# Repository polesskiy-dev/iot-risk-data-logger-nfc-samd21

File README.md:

# IoT Risk Data Logger

## Introduction
Fully open-source and open-hardware **data logger** tailored for logistics applications i.e. for cold chain monitoring systems.

## Hardware

[Schematics, PCB, enclosure, BOM, assembly documentation](https://github.com/polesskiy-dev/iot-risk-data-logger-nfc-samd21-hardware)

### Features

#### Key risk metrics:
- Temperature/Humidity [Sensirion SHT3x](https://sensirion.com/media/documents/213E6A3B/63A5A569/Datasheet_SHT3x_DIS.pdf)
- Ambient Light Sensor [TI OPT3001](https://www.ti.com/lit/ds/symlink/opt3001.pdf?ts=1694786594042&ref_url=https%253A%252F%252Fwww.ti.com%252Fproduct%252FOPT3001)
- Shock Sensor - Accelerometer [NXP MMA8452Q](https://www.nxp.com/docs/en/data-sheet/MMA8452Q.pdf)

#### Communication:
- USB-C:
    - MSD: Device works ad a flash drive to direct log read on PC
    - CDC: Console for debug and firmware bootloader
- NFC for control through mobile app [ST ST25DV04K](https://www.st.com/resource/en/datasheet/st25dv04k.pdf)

#### Security:
- Hardware crypto [Microchip ATECC608A](https://www.microchip.com/wwwproducts/en/ATECC608A) for:
    - Firmware encryption for bootloader
    - Log data encryption
    - Authentication (X509 certificates for IoT platforms)

#### Power:
- Powered by 2xAAA batteries or USB-C (reverse polarity protection, OR source selection)
- Low Power Consumption: Ultra-low power architecture, ~ one year of data acquisition

#### Additional Features:
- 4MB SPI NOR Flash [AT25DF321](https://www.mouser.com/catalog/specsheets/atmel_doc3669.pdf?_gl=1*5ifz1l*_ga*NTg5MTc1OTE2LjE2ODkwMTAyMDY.*_ga_15W4STQT4T*MTY5NDg2NDM4MS4yMS4wLjE2OTQ4NjQzODIuMC4wLjA.*_ga_1KQLCYKRX3*MTY5NDg2NDM4MS4yMS4wLjE2OTQ4NjQzODIuNTkuMC4w)
- RTC Clock: accurate 32.768Hz quartz oscillator
- LED: Simple indication for device states

#### Main MCU
- [Microchip ATSAMD21E18](https://www.microchip.com/en-us/product/atsamd21e18) - 32-bit ARM Cortex-M0+ MCU, 48MHz, 256KB of flash and 32KB of SRAM. Satisfies AEC-Q100, recommended for Automotive.

## Firmware

The firmware is written in C with a bare-metal approach and exclusively uses static memory allocation. It is developed on top of the [Harmony v3](https://www.microchip.com/en-us/tools-resources/configure/mplab-harmony) Embedded Software framework. Developed with [MPLAB X](https://www.microchip.com/en-us/tools-resources/develop/mplab-x-ide), [XC32](https://www.microchip.com/en-us/tools-resources/develop/mplab-xc-compilers) compiler.

### Main architecture

The source code adheres to an asynchronous, non-blocking programming style designed to achieve ultra-low power consumption.

The core mechanism revolves around handling asynchronous events from a queue and entering a low-power sleep state when the queue is empty. New events are enqueued either through interrupts (e.g., cron-scheduled sensor reads) or through the main system loop.

The architecture incorporates the following key concepts:
- [Event Loop](https://en.wikipedia.org/wiki/Event_loop)
- [Actor Model](https://en.wikipedia.org/wiki/Actor_model) - aka [Active Object](https://en.wikipedia.org/wiki/Active_object)
- [Finite-state machine](https://en.wikipedia.org/wiki/Finite-state_machine) - [Mealy](https://en.wikipedia.org/wiki/Mealy_machine) + [Moore](https://en.wikipedia.org/wiki/Moore_machine) implementation

To streamline development, an Active Object + FSM library has been implemented and is maintained in a separate [active-object-fsm](https://github.com/polesskiy-dev/active-object-fsm) repository.

## Installation
    
    $ git clone https://github.com/polesskiy-dev/iot-risk-data-logger-nfc-samd21 --recurse-submodules

Update submodules to the latest version (optional):

    $ git submodule init && git submodule update --remote # install submodules

## Some dev process photos:

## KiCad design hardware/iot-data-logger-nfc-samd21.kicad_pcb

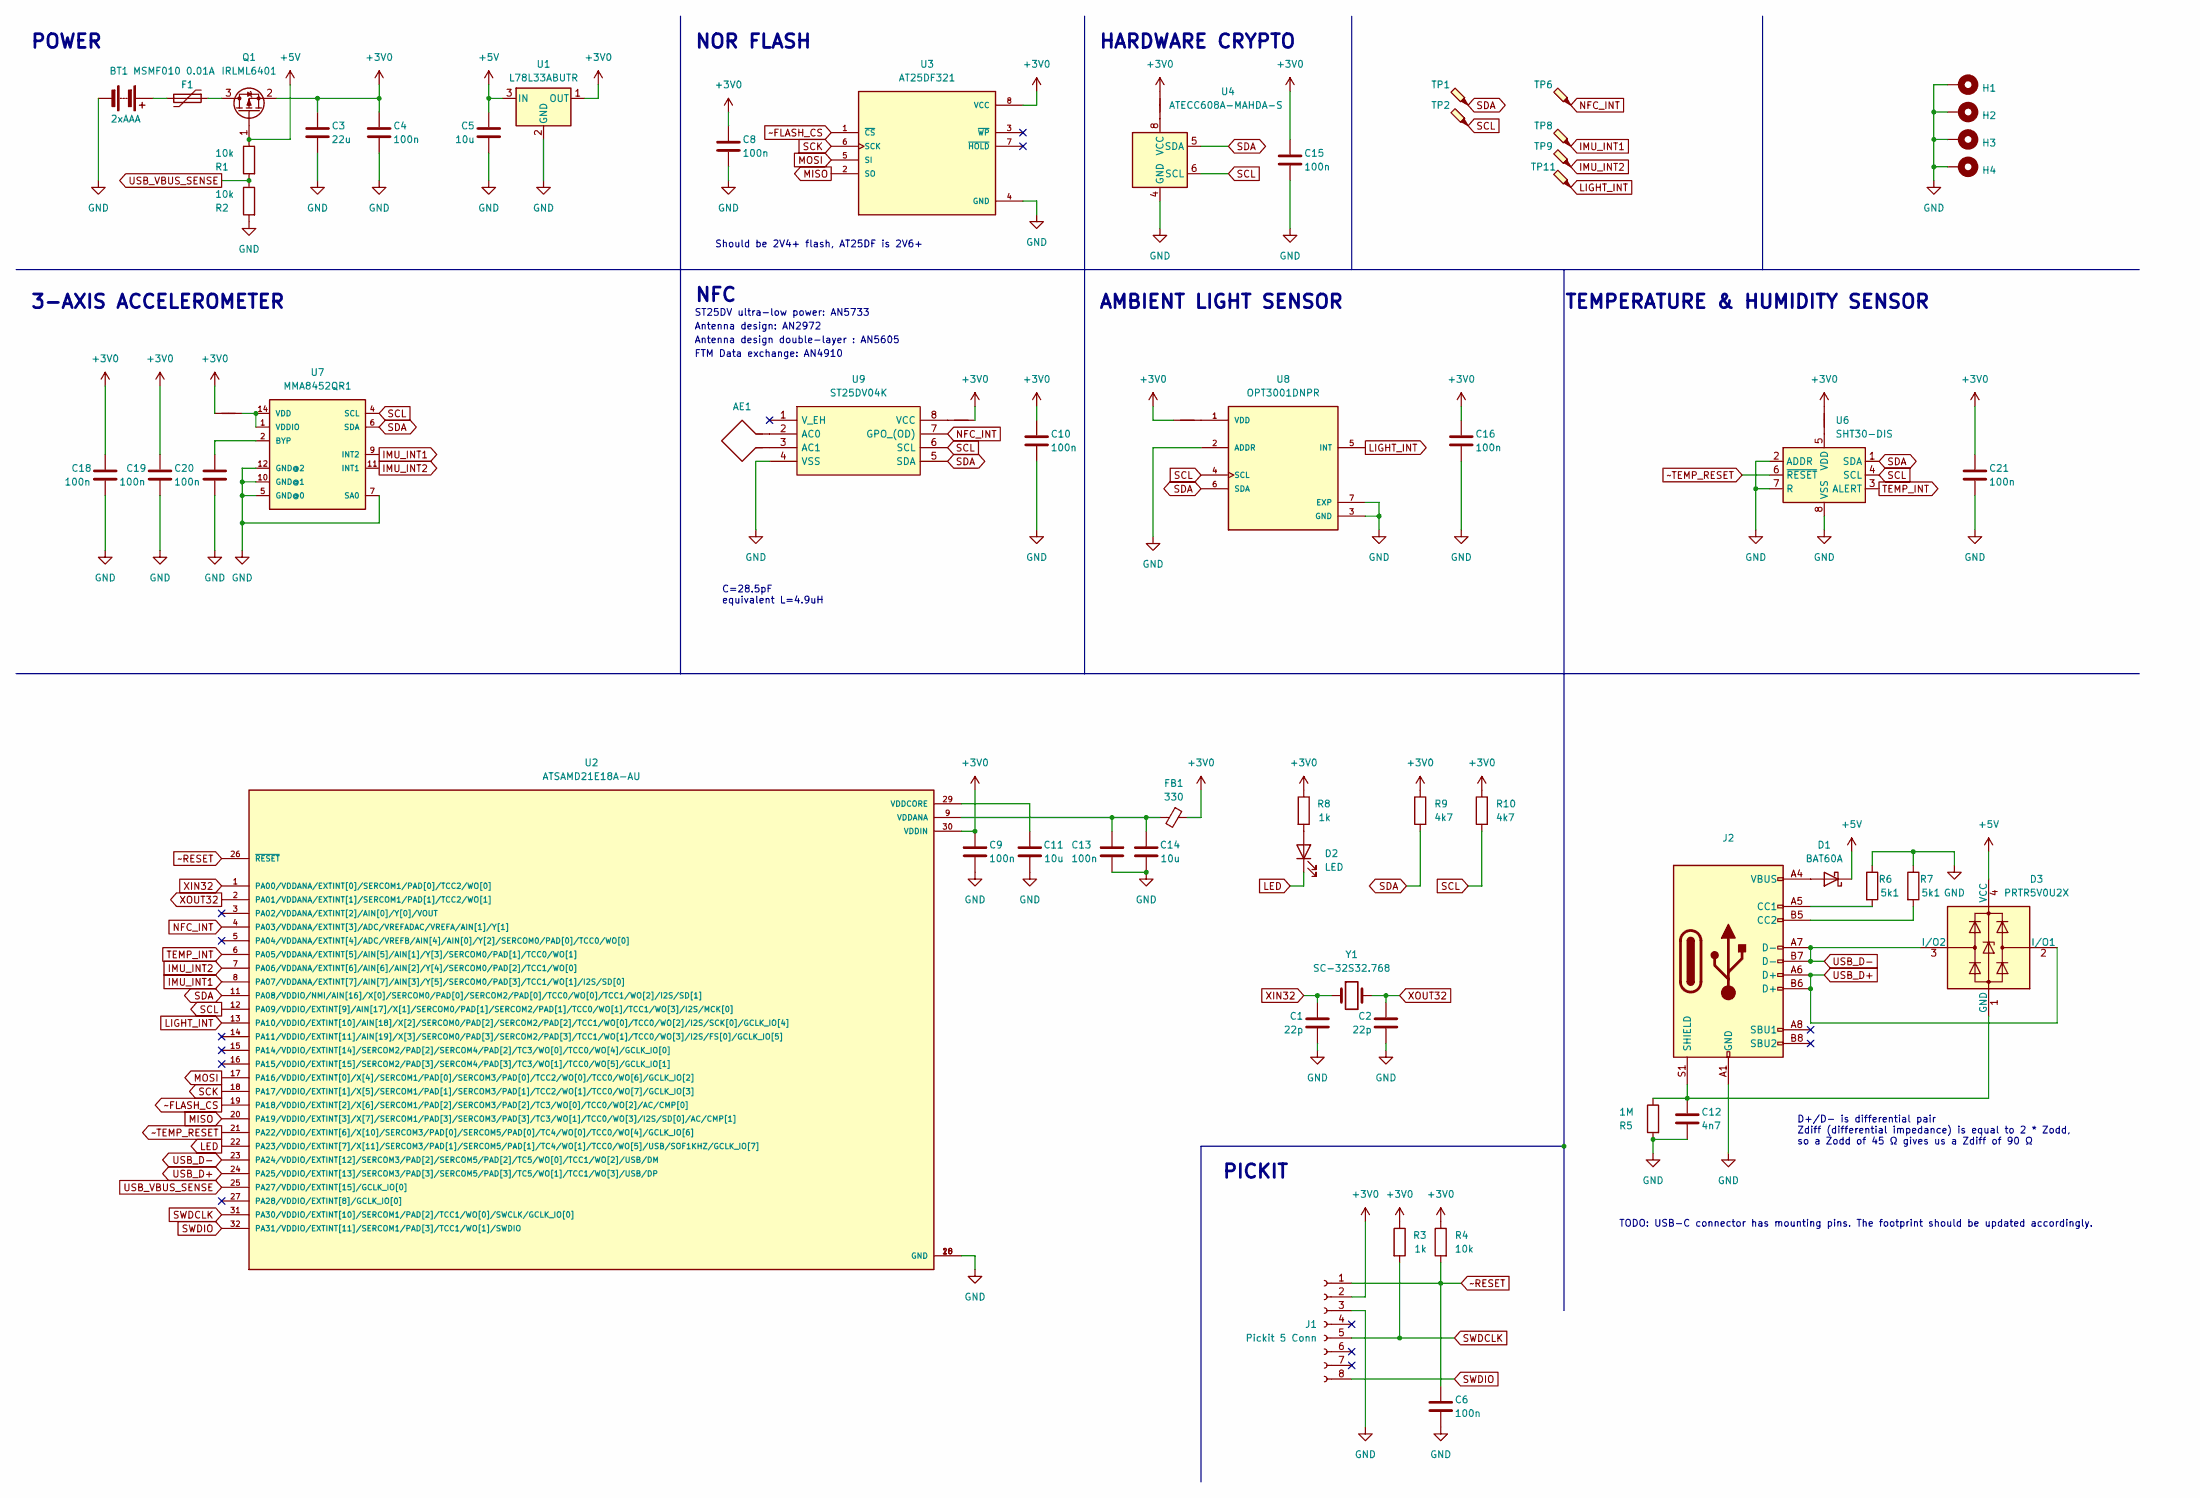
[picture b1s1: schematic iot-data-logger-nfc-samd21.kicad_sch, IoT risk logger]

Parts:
AE1: Antenna_Loop; ANT_NFC_30x40
BT1: 2xAAA; BatteryHolder_Keystone_2468_2xAAA; Part Keystone 2468; LCSC Part C254917
C1, C2: 22p; C_0805_2012Metric_Pad1.18x1.45mm_HandSolder; Part CL21C220JBANNNC; LCSC Part C1804
C3: 22u; C_1206_3216Metric_Pad1.33x1.80mm_HandSolder; Part CL31A226KAHNNNE; LCSC Part C12891
C4, C6, C8, C9, C10, C13, C15, C16, C18, C19, C20, C21: 100n; C_0805_2012Metric_Pad1.18x1.45mm_HandSolder; Part CL21B104KBCNNNC; LCSC Part C1711
C5, C11, C14: 10u; C_0805_2012Metric_Pad1.18x1.45mm_HandSolder; Part CL21A106KOQNNNE; LCSC Part C1713
C12: 4n7; C_0805_2012Metric_Pad1.18x1.45mm_HandSolder; Part CL21B472KBANNNC; LCSC Part C50131
D1: BAT60A; D_SOD-323_HandSoldering; Part BAT60A; LCSC Part C5355496
D2: LED; LED_0805_2012Metric_Pad1.15x1.40mm_HandSolder; Part NCD0805G1; LCSC Part C84260
D3: PRTR5V0U2X; SOT-143; Part PRTR5V0U2X; LCSC Part C2827688
F1: MSMF010 0.01A; Fuse_1812_4532Metric_Pad1.30x3.40mm_HandSolder; Part MF-MSMF010-2; LCSC Part C12430
FB1: 330; R_0805_2012Metric_Pad1.20x1.40mm_HandSolder; Part BLM21PG331SN1D; LCSC Part C47130
H1, H2, H3, H4: MountingHole_Pad; MountingHole_3.2mm_M3_Pad_Via
J1: Pickit 5 Conn; PinSocket_1x08_P2.54mm_Vertical
J2: USB Type-C; USB_C_Receptacle_XKB_U262-16XN-4BVC11; Part KH-TYPE-C-16P; LCSC Part C709357
NT1, NT2, NT3, NT4, NT5: NetTie_2; NetTie-2_SMD_Pad0.5mm
Q1: IRLML6401; SOT-23; Part IRLML6401TRPBF; LCSC Part C3034
R1, R2, R4: 10k; R_0805_2012Metric_Pad1.20x1.40mm_HandSolder; Part RC0805FR-0710KL; LCSC Part C84376
R3, R8: 1k; R_0805_2012Metric_Pad1.20x1.40mm_HandSolder; Part RC0805FR-071KL; LCSC Part C95781
R5: 1M; R_0805_2012Metric_Pad1.20x1.40mm_HandSolder; Part RC0805FR-071ML; LCSC Part C107700
R6, R7: 5k1; R_0805_2012Metric_Pad1.20x1.40mm_HandSolder; Part RC0805FR-075K1L; LCSC Part C84375
R9, R10: 4k7; R_0805_2012Metric_Pad1.20x1.40mm_HandSolder; Part RC0805FR-074K7L; LCSC Part C60816
TP1, TP2, TP6, TP8, TP9, TP11: TestPoint_Probe; TestPoint_THTPad_D1.5mm_Drill0.7mm
U1: L78L33ABUTR; SOT-89-3_Handsoldering; Part L78L33ABUTR; LCSC Part C81362
U2: ATSAMD21E18A-AU; TQFP-32_7x7mm_P0.8mm; Part ATSAMD21E18A-AU; LCSC Part C618771
U3: AT25DF321; SOP-8_5.28x5.23mm_P1.27mm; Part AT25DF321A-SH-T; LCSC Part C6490
U4: ATECC608A-MAHDA-S; DFN-8-1EP_3x2mm_P0.5mm_EP1.3x1.5mm; Part ATECC608A-MAHDA-S; LCSC Part C616908
U6: SHT30-DIS; Sensirion_DFN-8-1EP_2.5x2.5mm_P0.5mm_EP1.1x1.7mm; Part SHT30-DIS-B10KS; LCSC Part C2687423
U7: MMA8452QR1; XDCR_MMA8452QR1; Part MMA8452QR1; LCSC Part C11360
U8: OPT3001DNPR; SON65P200X200X65-7N; Part OPT3001DNPR; LCSC Part C90462
U9: ST25DV04K; TSSOP-8_4.4x3mm_P0.65mm; Part ST25DV04K-IER6T3; LCSC Part C2654816
Y1: SC-32S32.768; Crystal_SMD_EuroQuartz_EQ161-2Pin_3.2x1.5mm_HandSoldering; Part SC-32S32.768kHz20PPM12.5pF; LCSC Part C97606

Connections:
+3V0: C3.1, C4.1, C8.1, C9.1, C10.1, C15.1, C16.1, C18.1, C19.1, C21.1, FB1.1, J1.2, NT1.1, NT2.1, NT3.2, NT4.1, NT5.2, Q1.2 (S), R3.1, R4.1, R8.1, R9.1, R10.1, U1.1 (OUT), U2.30 (VDDIN), U3.8 (VCC)
+5V: C5.1, D1.1 (K), D3.4 (VCC), Q1.1 (G), R1.1, U1.3 (IN)
GND: BT1.2 (-), C1.2, C2.2, C3.2, C4.2, C5.2, C6.2, C8.2, C9.2, C10.2, C11.2, C12.2, C13.2, C14.2, C15.2, C16.2, C18.2, C19.2, C20.2, C21.2, H1.1, H2.1, H3.1, H4.1, J1.3, J2.A1 (GND), J2.A12 (GND), J2.B1 (GND), J2.B12 (GND), R2.2, R5.2, R6.1, R7.1, U1.2 (GND), U2.10 (GND), U2.28 (GND), U3.4 (GND), U4.4 (GND), U6.2 (ADDR), U6.7 (R), U6.8 (VSS), U6.9 (VSS), U7.5 (GND@0), U7.7 (SA0), U7.10 (GND@1), U7.12 (GND@2), U8.2 (ADDR), U8.3 (GND), U8.7 (EXP), U9.4 (VSS)
IMU_INT1: TP8.1, U2.8 (PA07/VDDANA/EXTINT[7]/AIN[7]/AIN[3]/Y[5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), U7.9 (INT2)
IMU_INT2: TP9.1, U2.7 (PA06/VDDANA/EXTINT[6]/AIN[6]/AIN[2]/Y[4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), U7.11 (INT1)
LED: D2.1 (K), U2.22 (PA23/VDDIO/EXTINT[7]/X[11]/SERCOM3/PAD[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)
LIGHT_INT: TP11.1, U2.13 (PA10/VDDIO/EXTINT[10]/AIN[18]/X[2]/SERC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), U8.5 (INT)
MISO: U2.20 (PA19/VDDIO/EXTINT[3]/X[7]/SERCOM1/PAD[3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), U3.2 (SO)
MOSI: U2.17 (PA16/VDDIO/EXTINT[0]/X[4]/SERCOM1/PAD[0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), U3.5 (SI)
NFC_INT: TP6.1, U2.4 (PA03/VDDANA/EXTINT[3]/ADC/VREFADAC/VREF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), U9.7 (GPO_(OD))
unnamed: BT1.1 (+), F1.2
unnamed: D1.2 (A), J2.A4 (VBUS), J2.A9 (VBUS), J2.B4 (VBUS), J2.B9 (VBUS)
unnamed: D2.2 (A), R8.2
unnamed: C12.1, D3.1 (GND), J2.S1 (SHIELD), R5.1
unnamed: J2.A5 (CC1), R6.2
unnamed: J2.B5 (CC2), R7.2
unnamed: F1.1, Q1.3 (D)
unnamed: C13.1, C14.1, FB1.2, U2.9 (VDDANA)
unnamed: C11.1, U2.29 (VDDCORE)
unnamed: NT1.2, U4.8 (VCC)
unnamed: NT5.1, U6.5 (VDD)
unnamed: C20.1, U7.2 (BYP)
unnamed: NT2.2, U7.1 (VDDIO), U7.14 (VDD)
unnamed: NT4.2, U8.1 (VDD)
unnamed: AE1.2, U9.2 (AC0)
unnamed: AE1.1, U9.3 (AC1)
unnamed: NT3.1, U9.8 (VCC)
SCK: U2.18 (PA17/VDDIO/EXTINT[1]/X[5]/SERCOM1/PAD[1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), U3.6 (SCK)
SCL: R10.2, TP2.1, U2.12 (PA09/VDDIO/EXTINT[9]/AIN[17]/X[1]/SERCO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), U4.6 (SCL), U6.4 (SCL), U7.4 (SCL), U8.4 (SCL), U9.6 (SCL)
SDA: R9.2, TP1.1, U2.11 (PA08/VDDIO/NMI/AIN[16]/X[0]/SERCOM0/PAD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), U4.5 (SDA), U6.1 (SDA), U7.6 (SDA), U8.6 (SDA), U9.5 (SDA)
SWDCLK: J1.5, R3.2, U2.31 (PA30/VDDIO/EXTINT[10]/SERCOM1/PAD[2]/TC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)
SWDIO: J1.8, U2.32 (PA31/VDDIO/EXTINT[11]/SERCOM1/PAD[3]/TC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)
TEMP_INT: U2.6 (PA05/VDDANA/EXTINT[5]/AIN[5]/AIN[1]/Y[3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), U6.3 (ALERT)
USB_D+: D3.2 (I/O1), J2.A6 (D+), J2.B6 (D+), U2.24 (PA25/VDDIO/EXTINT[13]/SERCOM3/PAD[3]/SE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)
USB_D-: D3.3 (I/O2), J2.A7 (D-), J2.B7 (D-), U2.23 (PA24/VDDIO/EXTINT[12]/SERCOM3/PAD[2]/SE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)
USB_VBUS_SENSE: R1.2, R2.1, U2.25 (PA27/VDDIO/EXTINT[15]/GCLK_IO[0])
XIN32: C1.1, U2.1 (PA00/VDDANA/EXTINT[0]/SERCOM1/PAD[0]/TC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), Y1.1
XOUT32: C2.1, U2.2 (PA01/VDDANA/EXTINT[1]/SERCOM1/PAD[1]/TC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), Y1.2
~FLASH_CS: U2.19 (PA18/VDDIO/EXTINT[2]/X[6]/SERCOM1/PAD[2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), U3.1 (~CS)
~RESET: C6.1, J1.1, R4.2, U2.26 (~RESET)
~TEMP_RESET: U2.21 (PA22/VDDIO/EXTINT[6]/X[10]/SERCOM3/PAD[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), U6.6 (~RESET)

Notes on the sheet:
Antenna design double-layer : AN5605
HARDWARE CRYPTO
FTM Data exchange: AN4910
TODO: USB-C connector has mounting pins. The footprint should be updated accordingly.
NFC
С=28.5pF equivalent L=4.9uH
D+/D- is differential pair Zdiff (differential impedance) is equal to 2 * Zodd, so a Zodd of 45 Ω gives us a Zdiff of 90 Ω
Antenna design: AN2972
POWER
ST25DV ultra-low power: AN5733
Should be 2V4+ flash, AT25DF is 2V6+
3-AXIS ACCELEROMETER
PICKIT
NOR FLASH
TEMPERATURE & HUMIDITY SENSOR
AMBIENT LIGHT SENSOR

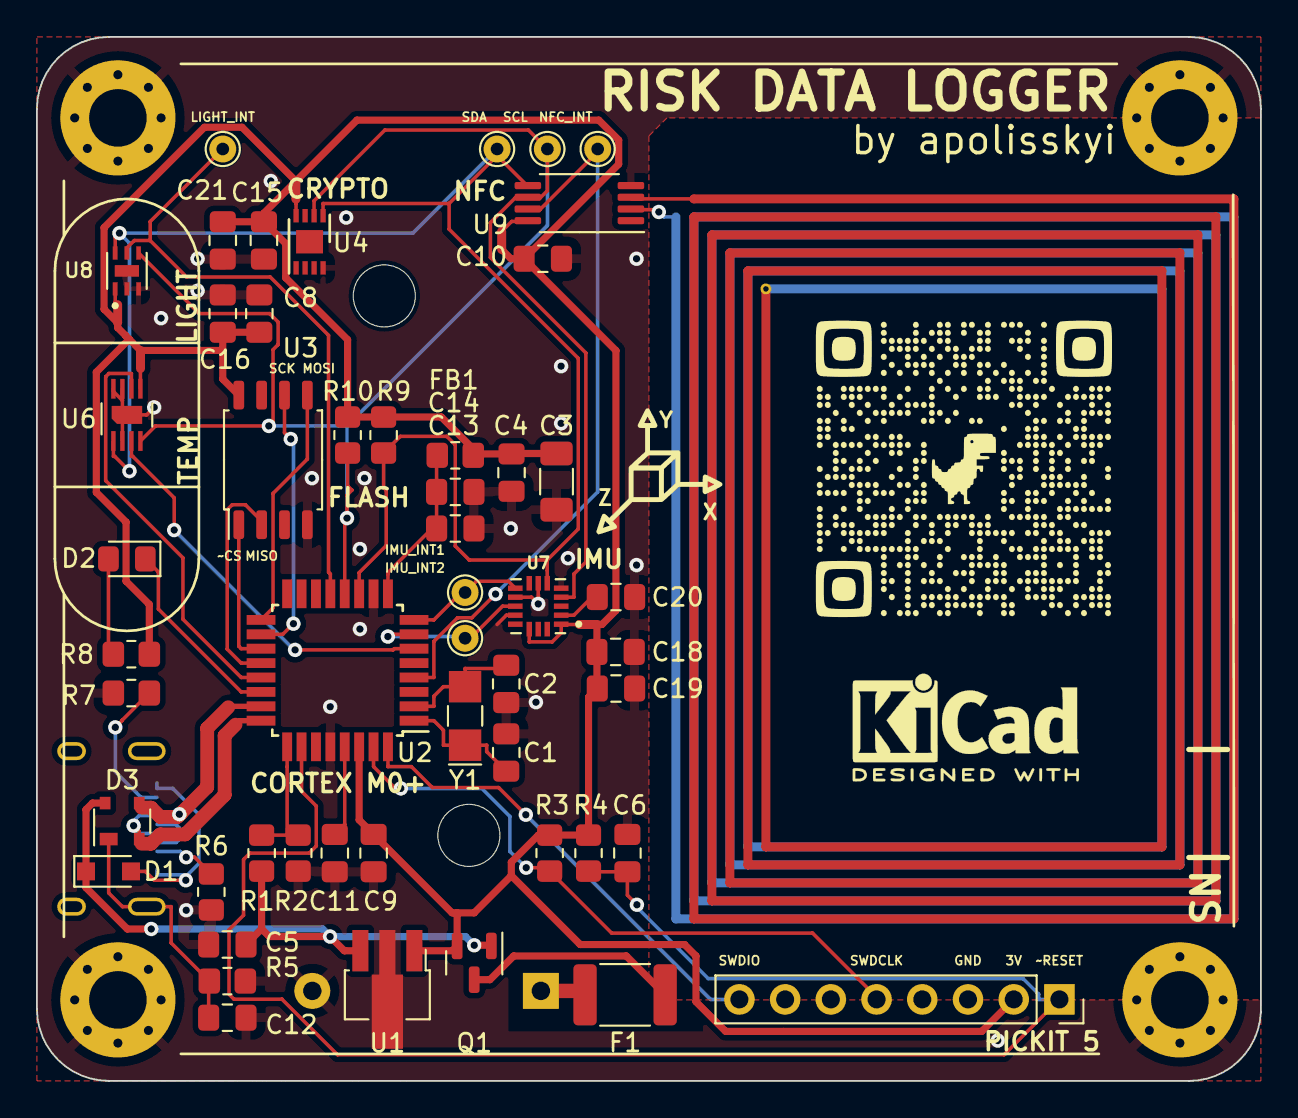
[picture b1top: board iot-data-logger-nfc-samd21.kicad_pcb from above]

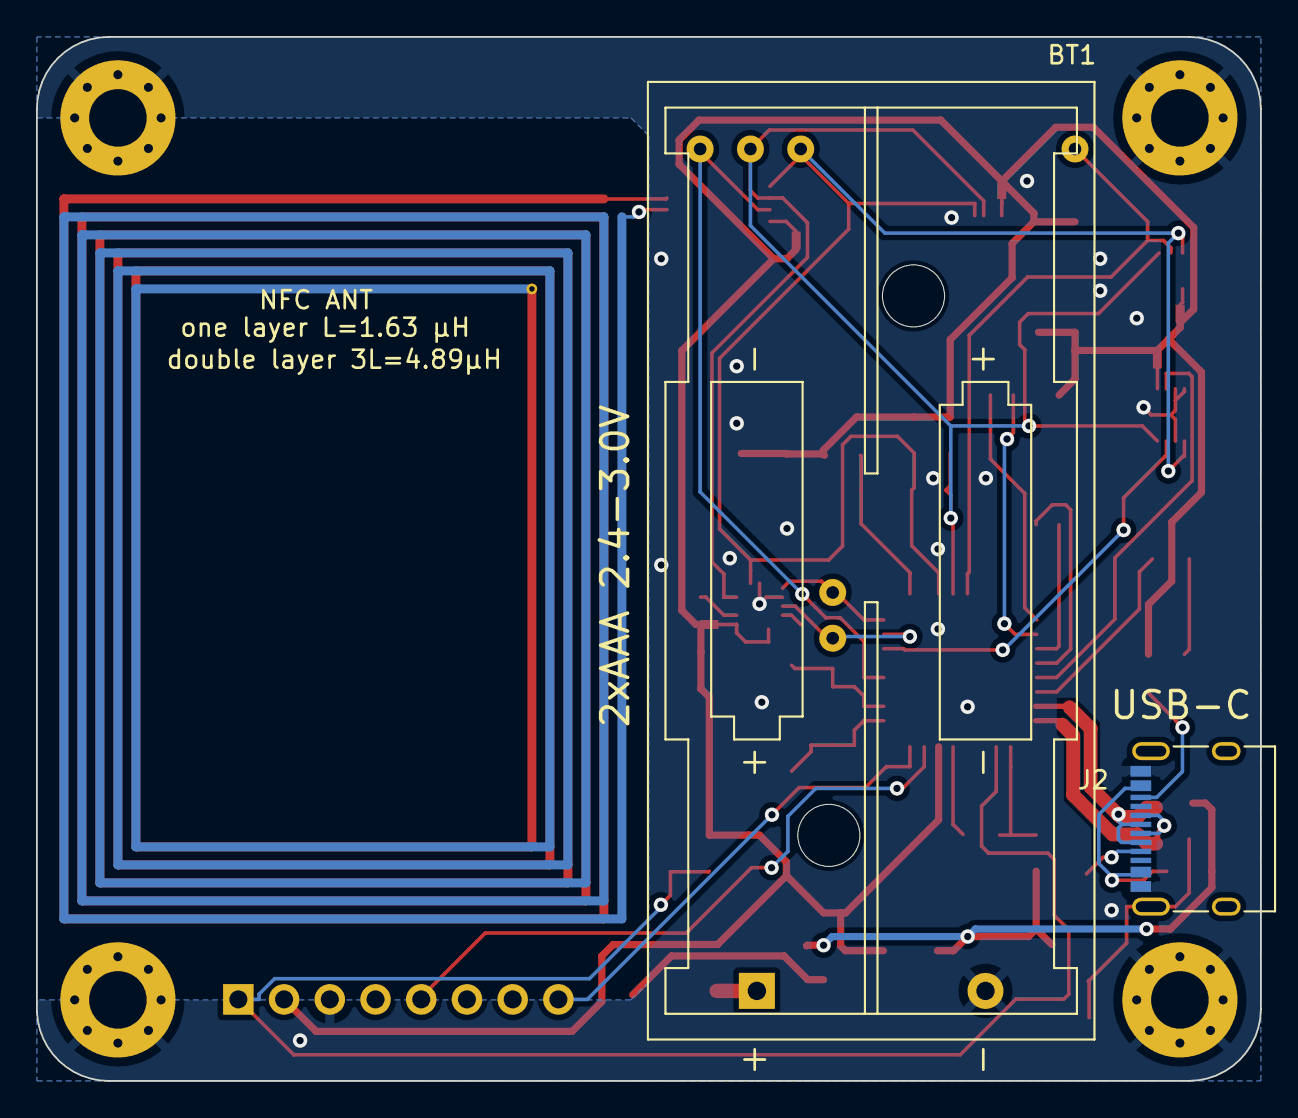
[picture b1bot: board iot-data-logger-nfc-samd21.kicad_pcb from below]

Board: 2 copper layers, 68.0 x 58.0 mm, 64 parts (2 on the bottom side), 41 nets.

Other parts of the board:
G04: LOGO

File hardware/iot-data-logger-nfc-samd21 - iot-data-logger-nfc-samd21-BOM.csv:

Item,Qty,Designator,Value,LibPart,Package/Footprint ,Datasheet,LCSC Part,LCSC Part ALT,Mfg Part #,URL,URL ALT
1,1,BT1,2xAAA,Device:Battery,Battery:BatteryHolder_Keystone_2468_2xAAA,https://datasheet.lcsc.com/lcsc/2303201800_Keystone-2468_C25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,C254917,,Keystone 2468,https://www.lcsc.com/product-detail/Battery-Connectors_Keyst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,
2,2,"C1, C2",22p,Device:C,Capacitor_SMD:C_0805_2012Metric_Pad1.18x1.45mm_HandSolder,~,C1804,,CL21C220JBANNNC,https://www.lcsc.com/product-detail/Multilayer-Ceramic-Capac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,
3,1,C3,22u,Device:C,Capacitor_SMD:C_1206_3216Metric_Pad1.33x1.80mm_HandSolder,~,C12891,,CL31A226KAHNNNE,https://www.lcsc.com/product-detail/Multilayer-Ceramic-Capac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,
4,12,"C4, C6, C8, C9, C10, C13, C15, C16, C18, C19, C20, C21",100n,Device:C,Capacitor_SMD:C_0805_2012Metric_Pad1.18x1.45mm_HandSolder,~,C1711,,CL21B104KBCNNNC,https://www.lcsc.com/product-detail/Multilayer-Ceramic-Capac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,
5,3,"C5, C11, C14",10u,Device:C,Capacitor_SMD:C_0805_2012Metric_Pad1.18x1.45mm_HandSolder,~,C1713,,CL21A106KOQNNNE,https://www.lcsc.com/product-detail/Multilayer-Ceramic-Capac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,
6,1,C12,4n7,Device:C,Capacitor_SMD:C_0805_2012Metric_Pad1.18x1.45mm_HandSolder,~,C50131,,CL21B472KBANNNC,https://www.lcsc.com/product-detail/Multilayer-Ceramic-Capac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,
7,1,D1,BAT60A,Diode:BAT60A,Diode_SMD:D_SOD-323_HandSoldering,https://www.infineon.com/dgdl/Infineon-BAT60ASERIES-DS-v01_0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,C5355496,,BAT60A,https://www.lcsc.com/product-detail/Schottky-Barrier-Diodes-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,
8,1,D2,LED,Device:LED,LED_SMD:LED_0805_2012Metric_Pad1.15x1.40mm_HandSolder,~,C84260,,NCD0805G1,https://www.lcsc.com/product-detail/Light-Emitting-Diodes-LE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,
9,1,D3,PRTR5V0U2X,Power_Protection:PRTR5V0U2X,Package_TO_SOT_SMD:SOT-143,https://assets.nexperia.com/documents/data-sheet/PRTR5V0U2X.pdf,C2827688,,PRTR5V0U2X,https://www.lcsc.com/product-detail/ESD-Protection-Devices_T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,
10,1,F1,MSMF010 0.01A,Device:Polyfuse,Fuse:Fuse_1812_4532Metric_Pad1.30x3.40mm_HandSolder,~,C12430,,MF-MSMF010-2,https://www.lcsc.com/product-detail/Resettable-Fuses_BOURNS-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,
11,1,FB1,330Ω@100MHz Ferrite,Device:FerriteBead_Small,Resistor_SMD:R_0805_2012Metric_Pad1.20x1.40mm_HandSolder,~,C47130,,BLM21PG331SN1D,https://www.lcsc.com/product-detail/Ferrite-Beads_Murata-Ele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,
12,1,J2,USB Type-C,Connector:USB_C_Receptacle_USB2.0,Connector_USB:USB_C_Receptacle_XKB_U262-16XN-4BVC11,https://datasheet.lcsc.com/lcsc/2009111434_Shenzhen-Kinghelm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,C709357,,KH-TYPE-C-16P,https://www.lcsc.com/product-detail/USB-Connectors_Shenzhen-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,
13,1,Q1,IRLML6401,Device:Q_PMOS_GSD,Package_TO_SOT_SMD:SOT-23,~,C3034,,IRLML6401TRPBF,https://www.lcsc.com/product-detail/MOSFETs_Infineon-Technol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,
14,3,"R1, R2, R4",10k,Device:R,Resistor_SMD:R_0805_2012Metric_Pad1.20x1.40mm_HandSolder,~,C84376,,RC0805FR-0710KL,https://www.lcsc.com/product-detail/Chip-Resistor-Surface-Mo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,
15,2,"R3, R8",1k,Device:R,Resistor_SMD:R_0805_2012Metric_Pad1.20x1.40mm_HandSolder,~,C95781,,RC0805FR-071KL,https://www.lcsc.com/product-detail/Chip-Resistor-Surface-Mo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,
16,1,R5,1M,Device:R,Resistor_SMD:R_0805_2012Metric_Pad1.20x1.40mm_HandSolder,~,C107700,,RC0805FR-071ML,https://www.lcsc.com/product-detail/Chip-Resistor-Surface-Mo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,
17,2,"R6, R7",5k1,Device:R,Resistor_SMD:R_0805_2012Metric_Pad1.20x1.40mm_HandSolder,~,C84375,,RC0805FR-075K1L,https://www.lcsc.com/product-detail/Chip-Resistor-Surface-Mo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,
18,2,"R9, R10",4k7,Device:R,Resistor_SMD:R_0805_2012Metric_Pad1.20x1.40mm_HandSolder,~,C60816,,RC0805FR-074K7L,https://www.lcsc.com/product-detail/Chip-Resistor-Surface-Mo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,
19,1,U1,L78L33ABUTR,Regulator_Linear:L78L33_SOT89,Package_TO_SOT_SMD:SOT-89-3_Handsoldering,http://www.st.com/content/ccc/resource/technical/document/da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,C81362,,L78L33ABUTR,https://www.lcsc.com/product-detail/Linear-Voltage-Regulator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,
20,1,U2,ATSAMD21E18A-AU,ATSAMD21E17A-AUT:ATSAMD21E17A-AUT,Package_QFP:TQFP-32_7x7mm_P0.8mm,https://datasheet.lcsc.com/lcsc/2210180700_Microchip-Tech-AT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,C618771,C618770,ATSAMD21E18A-AU,https://www.lcsc.com/product-detail/Microcontroller-Units-MC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,https://www.lcsc.com/product-detail/Microcontroller-Units-MC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
21,1,U3,AT25DF321,AT25DF041B-XMHN-B:AT25DF041B-XMHN-B,Package_SO:SOP-8_5.28x5.23mm_P1.27mm,https://datasheet.lcsc.com/lcsc/1811091709_Dialog-Semiconduc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,C6490,,AT25DF321A-SH-T,https://www.lcsc.com/product-detail/NOR-FLASH_Dialog-Semicon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,
22,1,U4,ATECC608A-MAHDA-S,Security:ATECC608A-SSHDA,Package_DFN_QFN:DFN-8-1EP_3x2mm_P0.5mm_EP1.3x1.5mm,http://ww1.microchip.com/downloads/en/DeviceDoc/ATECC608A-Cr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,C616908,,ATECC608A-MAHDA-S,https://www.lcsc.com/product-detail/Security-Verification-En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,
23,1,U6,SHT30-DIS,Sensor_Humidity:SHT30-DIS,Sensor_Humidity:Sensirion_DFN-8-1EP_2.5x2.5mm_P0.5mm_EP1.1x1.7mm,https://www.sensirion.com/fileadmin/user_upload/customers/se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,C2687423,,SHT30-DIS-B10KS,https://www.lcsc.com/product-detail/Temperature-and-Humidity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,
24,1,U7,MMA8452QR1,MMA8452Q:MMA8452Q,Personal:XDCR_MMA8452QR1,https://datasheet.lcsc.com/lcsc/1806121726_NXP-Semicon-MMA84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,C11360,,MMA8452QR1,https://www.lcsc.com/product-detail/Attitude-Sensor-Gyroscop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,
25,1,U8,OPT3001DNPR,OPT3001DNPR:OPT3001DNPR,Personal:SON65P200X200X65-7N,,C90462,,OPT3001DNPR,https://www.lcsc.com/product-detail/Ambient-Light-Sensors_Te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,
26,1,U9,ST25DV04K,ST25DV64K-IER8T3:ST25DV64K-IER8T3,Package_SO:TSSOP-8_4.4x3mm_P0.65mm,https://datasheet.lcsc.com/lcsc/2304140030_STMicroelectronic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,C2654816,,ST25DV04K-IER6T3,https://www.lcsc.com/product-detail/RF-Chips_STMicroelectron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,
27,1,Y1,SC-32S32.768,Device:Crystal,Crystal:Crystal_SMD_EuroQuartz_EQ161-2Pin_3.2x1.5mm_HandSoldering,~,C97606,,SC-32S32.768kHz20PPM12.5pF,https://www.lcsc.com/product-detail/Crystals_Seiko-SC-32S32-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,

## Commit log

2022-10-25 PCB: add qr to github repo
2022-11-22 add enclosure, bom docs
2022-11-22 add interactive BOM link
2022-11-26 generate Microchip Harmony 3 project, configure clock source
2022-11-26 add gpio pins assignment
2022-11-27 configure SERCOM0, SERCOM1, RTC peripherial libraries, draft FreeRTOS config
2022-11-27 add TIME, I2C driver to project graph, set USB ID
2022-11-28 add FreeRTOS tasks draf in project graph
2022-11-28 add app_usb.h/.c source code from Harmony v3 SAM MCU example
2022-11-28 get rid of Harmony v3 USB example temperature read legacy, make project compilable
2023-01-24 upgrade PCB with CS pin, NFC pull-up
2023-01-26 update PCB images
2023-02-04 pcb images: replace by renders
2023-08-09 shematics, PCB, BOM: update, prepare for SMT order, change light sensor to OPT3001
2023-08-27 update hardware, add enclosure drawings
2023-08-28 docs: add enclosure README draft
2023-08-28 docs: enclosure, add more pictures to README
2023-09-07 extracted hardware to https://github.com/polesskiy-dev/iot-risk-data-logger-nfc-samd21-hardware
2023-09-07 fresh project bootstraped
2023-09-11 initial: set _LED and TIME, initial blinky works
2023-09-11 initial: setup clocks
2023-09-11 initial: setup pins
2023-09-11 initial: add SERCOM0, I2C, RTC, PM, EIC, TODO: EIC check 5,6,7 channels
2023-09-11 initial: add SERCOM1, SPI AT25DF, MEMORY
2023-09-11 initial: add USB: MSD, CDC, CONSOLE, DEBUG
2023-09-12 initial: add FAT12 disk image, configure MSD, MEMORY
2023-09-12 initial: add CRYPTO Core, ATECC608
2023-09-12 add SHT3x initial sensor module, NFC initial module
2023-09-12 add .github with initial workflows build & gh pages
2023-09-12 intial: add libraries
2023-09-14 STORAGE, Boot sector: read, check, write. Temporary remove USB MSD
2023-09-16 create INIT Actor, add USB MSD
2023-09-16 enclosure: move to hardware repo
2023-09-19 STORAGE: add boot sector write, data store or request (unverified)
2023-09-21 NFC: add FT Mode enable sequence, temporary disable other modules
2023-09-24 NFC: add interrupt status read on GPO pulse, enable GPO interrupt pin _NFC_INT
2023-10-12 DEBUG: sht3x.c TODOs for debug simplification
2023-10-18 active-object-fsm: rename f according to new lib f names
2023-10-18 CI: fix docs
2023-10-21 INIT: rename to init_manager
2023-10-21 NFC: extract 'prepare mailbox' flow to sub-fsm
2023-10-25 NFC: add GPO interrupt
2023-10-25 APP,USB Managers: add main app and USB manager
2023-10-25 USB: Add USB_VBUS_SENSE Pin Interrupt handle
2023-11-17 NFC: configure GPO to inerrupt on RF message put/get
2023-11-17 deploy: 4c14f5153df9c01d96b5c7815d46cfb9047c46dd
2023-11-18 clean the firmware
2023-11-18 Initial configuration with FreeRTOS
2023-11-19 Configure Clock
2023-11-19 Configure RTC, USB MSD
2023-11-19 Configure Flash SPI, AT25DF Driver
2023-11-19 Configure NMI
2023-11-19 Configure pins
2023-11-19 Draft: add simple LED task on RTC interrupt
